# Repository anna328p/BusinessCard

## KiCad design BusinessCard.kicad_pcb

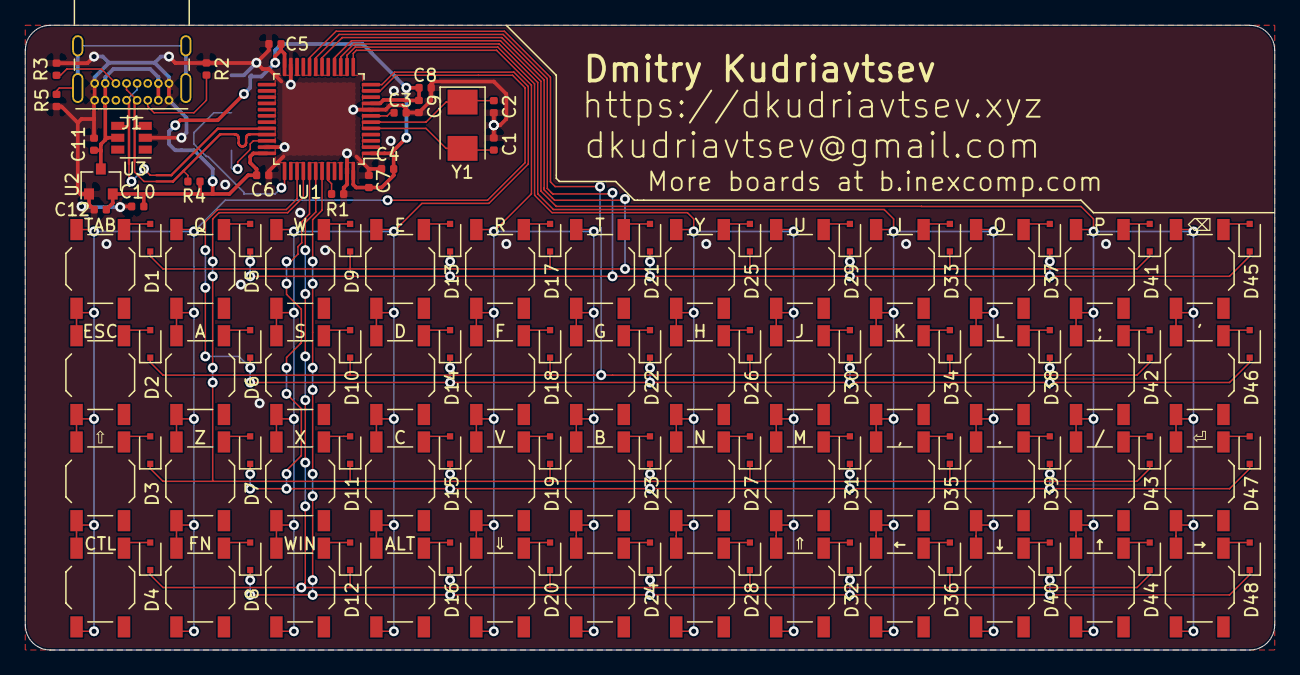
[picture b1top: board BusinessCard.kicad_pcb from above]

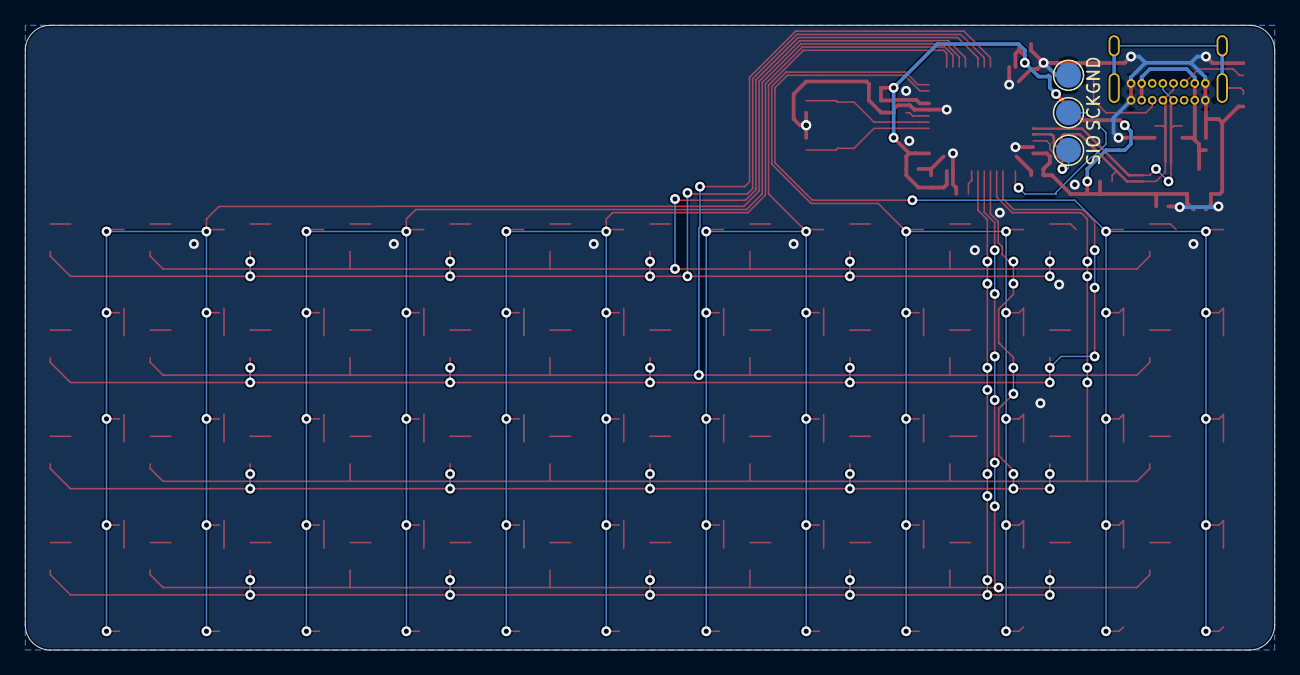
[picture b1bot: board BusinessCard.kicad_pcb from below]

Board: 2 copper layers, 100.0 x 50.0 mm, 121 parts (3 on the bottom side), 76 nets.

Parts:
C1, C2: 20pf; C_0402_1005Metric
C3, C4, C5, C6, C7, C9, C10: 100nf; C_0402_1005Metric
C8, C11, C12: 1uf; C_0402_1005Metric
D1, D2, D3, D4, D5, D6, D7, D8, D9, D10, D11, D12, D13, D14, D15, D16, D17, D18, D19, D20, D21, D22, D23, D24, D25, D26, D27, D28, D29, D30, D31, D32, D33, D34, D35, D36, D37, D38, D39, D40, D41, D42, D43, D44, D45, D46, D47, D48: D_Small; D_SOD-323F
GND1: TestPoint; TestPoint_Pad_D2.0mm
J1: USB_C_Receptacle_USB2.0; USB_C_Receptacle_GCT_USB4085
R1: 10k; R_0402_1005Metric
R2, R3: 5.1K; R_0402_1005Metric
R4: 1.5K; R_0402_1005Metric
R5: 1M; R_0402_1005Metric
SCK1: TestPoint; TestPoint_Pad_D2.0mm
SIO1: TestPoint; TestPoint_Pad_D2.0mm
SW1, SW2, SW3, SW4, SW5, SW6, SW7, SW8, SW9, SW10, SW11, SW12, SW13, SW14, SW15, SW16, SW17, SW18, SW19, SW20, SW21, SW22, SW23, SW24, SW25, SW26, SW27, SW28, SW29, SW30, SW31, SW32, SW33, SW34, SW35, SW36, SW37, SW38, SW39, SW40, SW41, SW42, SW43, SW44, SW45, SW46, SW47, SW48: SW_Push_45deg; SW_SPST_TL3342
U1: STM32F103C8Tx; LQFP-48_7x7mm_P0.5mm
U2: XC6206PxxxMR; SOT-23
U3: SRV05-4; SOT-23-6
Y1: 8MHz; Crystal_SMD_5032-2Pin_5.0x3.2mm

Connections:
+5V: C11.2, J1.A4, J1.A9, J1.B4, J1.B9, U2.3, U3.5
/MCU Support/CC1: J1.A5, R2.1
/MCU Support/CC2: J1.B5, R3.2
BOOT0: R1.1, U1.44
DA+: J1.A6, J1.B6, R4.2, U1.33, U3.3
DA-: J1.A7, J1.B7, U1.32, U3.4
GND: C1.2, C2.2, C3.2, C4.1, C5.1, C6.1, C7.1, C8.1, C9.1, C10.1, C11.1, C12.2, GND1.1, J1.A1, J1.A12, J1.B1, J1.B12, R1.2, R2.2, R3.1, R5.1, U1.8, U1.23, U1.35, U1.47, U2.1, U3.2
NRST: C3.1, U1.7
unnamed: D1.2, SW1.2
unnamed: D2.2, SW2.2
unnamed: D3.2, SW3.2
unnamed: D4.2, SW4.2
unnamed: D5.2, SW5.2
unnamed: D6.2, SW6.2
unnamed: D7.2, SW7.2
unnamed: D8.2, SW8.2
unnamed: D9.2, SW9.2
unnamed: D10.2, SW10.2
unnamed: D11.2, SW11.2
unnamed: D12.2, SW12.2
unnamed: D13.2, SW13.2
unnamed: D14.2, SW14.2
unnamed: D15.2, SW15.2
unnamed: D16.2, SW16.2
unnamed: D17.2, SW17.2
unnamed: D18.2, SW18.2
unnamed: D19.2, SW19.2
unnamed: D20.2, SW20.2
unnamed: D21.2, SW21.2
unnamed: D22.2, SW22.2
unnamed: D23.2, SW23.2
unnamed: D24.2, SW24.2
unnamed: D25.2, SW25.2
unnamed: D26.2, SW26.2
unnamed: D27.2, SW27.2
unnamed: D28.2, SW28.2
unnamed: D29.2, SW29.2
unnamed: D30.2, SW30.2
unnamed: D31.2, SW31.2
unnamed: D32.2, SW32.2
unnamed: D33.2, SW33.2
unnamed: D34.2, SW34.2
unnamed: D35.2, SW35.2
unnamed: D36.2, SW36.2
unnamed: D37.2, SW37.2
unnamed: D38.2, SW38.2
unnamed: D39.2, SW39.2
unnamed: D40.2, SW40.2
unnamed: D41.2, SW41.2
unnamed: D42.2, SW42.2
unnamed: D43.2, SW43.2
unnamed: D44.2, SW44.2
unnamed: D45.2, SW45.2
unnamed: D46.2, SW46.2
unnamed: D47.2, SW47.2
unnamed: D48.2, SW48.2
unnamed: J1.S1, R5.2
PD0: C1.1, U1.5, Y1.2
PD1: C2.1, U1.6, Y1.1
SWDCLK: SCK1.1, U1.37
SWDIO: SIO1.1, U1.34
VBAT: C4.2, C5.2, C6.2, C7.2, C8.2, C9.2, C10.2, C12.1, R4.1, U1.1, U1.9, U1.24, U1.36, U1.48, U2.2
col1: SW1.1, SW2.1, SW3.1, SW4.1, SW5.1, SW6.1, SW7.1, SW8.1, U1.11
col2: SW9.1, SW10.1, SW11.1, SW12.1, SW13.1, SW14.1, SW15.1, SW16.1, U1.12
col3: SW17.1, SW18.1, SW19.1, SW20.1, SW21.1, SW22.1, SW23.1, SW24.1, U1.13
col4: SW25.1, SW26.1, SW27.1, SW28.1, SW29.1, SW30.1, SW31.1, SW32.1, U1.14
col5: SW33.1, SW34.1, SW35.1, SW36.1, SW37.1, SW38.1, SW39.1, SW40.1, U1.15
col6: SW41.1, SW42.1, SW43.1, SW44.1, SW45.1, SW46.1, SW47.1, SW48.1, U1.16
row0: D1.1, D9.1, D17.1, D25.1, D33.1, D41.1, U1.18
row1: D5.1, D13.1, D21.1, D29.1, D37.1, D45.1, U1.19
row2: D2.1, D10.1, D18.1, D26.1, D34.1, D42.1, U1.20
row3: D6.1, D14.1, D22.1, D30.1, D38.1, D46.1, U1.39
row4: D3.1, D11.1, D19.1, D27.1, D35.1, D43.1, U1.40
row5: D7.1, D15.1, D23.1, D31.1, D39.1, D47.1, U1.41
row6: D4.1, D12.1, D20.1, D28.1, D36.1, D44.1, U1.42
row7: D8.1, D16.1, D24.1, D32.1, D40.1, D48.1, U1.43

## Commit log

2020-04-26 Added license
2020-05-02 Added proper silkscreen for keys
2020-05-02 Floated the shield
2020-05-02 Fixed bad routing
2020-05-02 Added netlist and BOM generator
2020-05-02 Added LCSC part references
2020-05-07 fixed footprint
